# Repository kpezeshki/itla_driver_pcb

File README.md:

Board is generally functional but improvements are possible:

1. The hole size for the meanwell power supply modules is too small, so the modules need to be hacked to fit.

2. The UART module is too far from the board edge. Need to check footprint and shift closer.

Use a 40 mm half-height fan to cool the ITLA.

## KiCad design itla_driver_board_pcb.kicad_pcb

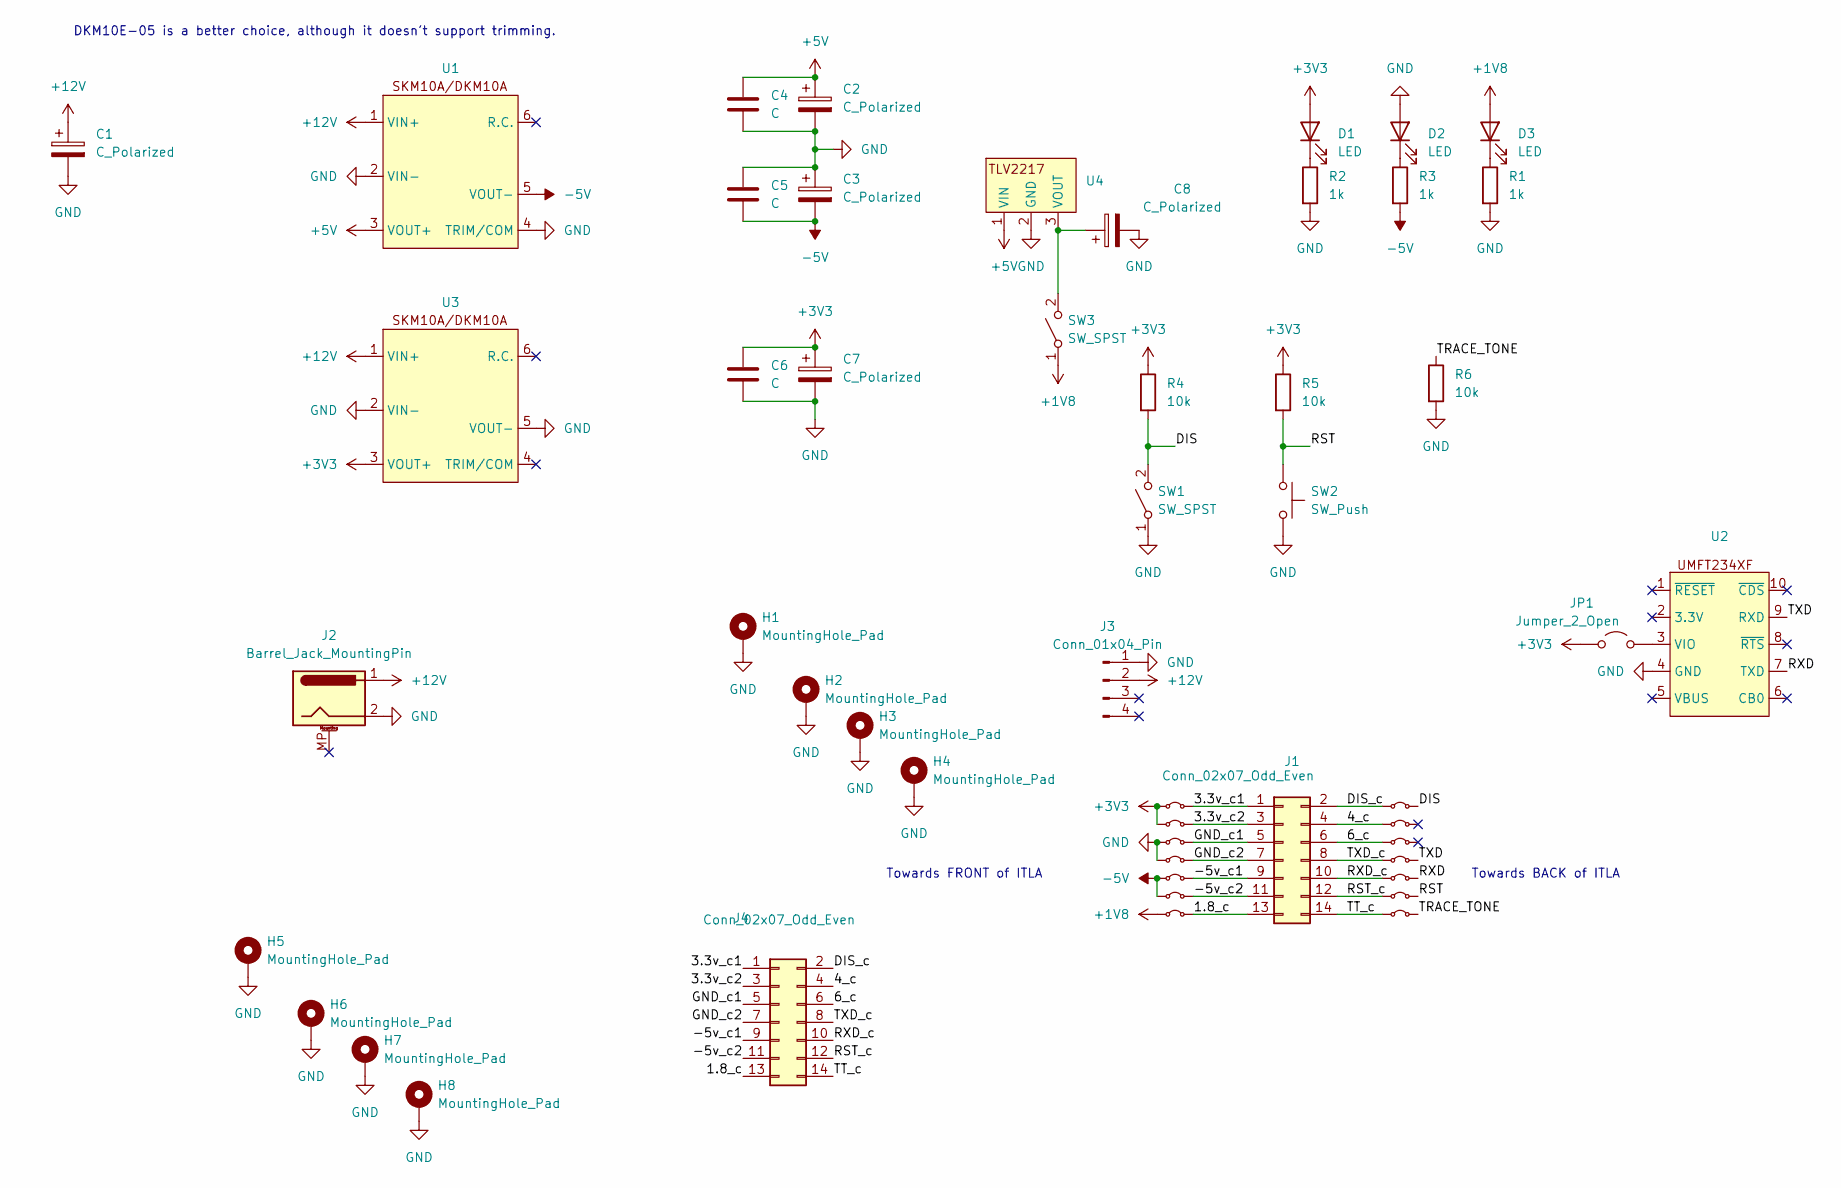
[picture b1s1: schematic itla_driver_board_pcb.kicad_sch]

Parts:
C1, C2, C3, C7, C8: C_Polarized; CP_Radial_D12.5mm_P5.00mm
C4, C5, C6: C; C_Disc_D10.0mm_W2.5mm_P5.00mm
D1, D2, D3: LED; LED_D5.0mm
H1, H2, H3, H4, H5, H6, H7, H8: MountingHole_Pad; MountingHole_3.2mm_M3_Pad
J1: Conn_02x07_Odd_Even; PinHeader_2x07_P1.00mm_Vertical_SMD
J2: Barrel_Jack_MountingPin; BarrelJack_CUI_PJ-063AH_Horizontal
J3: Conn_01x04_Pin; PinHeader_1x04_P2.54mm_Vertical
J4: Conn_02x07_Odd_Even; ITLA
JP1: Jumper_2_Open; SolderJumper-2_P1.3mm_Open_Pad1.0x1.5mm
JP2, JP3, JP4, JP5, JP6, JP7, JP8, JP9, JP10, JP11, JP12, JP13, JP14, JP15: Jumper_2_Small_Bridged; SolderJumper-2_P1.3mm_Bridged_Pad1.0x1.5mm
R1, R2, R3: 1k; R_Axial_DIN0207_L6.3mm_D2.5mm_P7.62mm_Horizontal
R4, R5, R6: 10k; R_Axial_DIN0207_L6.3mm_D2.5mm_P7.62mm_Horizontal
SW1, SW3: SW_SPST; SW_E-Switch_EG1271_SPDT
SW2: SW_Push; SW_SPST_Omron_B3F-40xx
U1, U3: SKM10
U2: UMFT234XF
U4: TO-220-3_Vertical

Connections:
+1V8: D3.2 (A), JP15.1 (A), SW3.1 (A)
+3V3: C6.1, C7.1, D1.2 (A), JP1.1 (A), JP9.1 (A), JP10.1 (A), R4.1, R5.1, U3.3 (VOUT+)
+5V: C2.1, C4.1, U1.3 (VOUT+), U4.1 (VIN)
+12V: C1.1, J2.1, J3.2, U1.1 (VIN+), U3.1 (VIN+)
-5V: C3.2, C5.2, JP13.1 (A), JP14.1 (A), R3.2, U1.5 (VOUT-)
/1.8_c: J1.13, J4.13, JP15.2 (B)
/3.3v_c1: J1.1, J4.1, JP9.2 (B)
/3.3v_c2: J1.3, J4.3, JP10.2 (B)
/4_c: J1.4, J4.4, JP7.1 (A)
/6_c: J1.6, J4.6, JP8.1 (A)
/-5v_c1: J1.9, J4.9, JP13.2 (B)
/-5v_c2: J1.11, J4.11, JP14.2 (B)
/DIS: JP2.2 (B), R4.2, SW1.2 (B)
/DIS_c: J1.2, J4.2, JP2.1 (A)
/GND_c1: J1.5, J4.5, JP11.2 (B)
/GND_c2: J1.7, J4.7, JP12.2 (B)
/RST: JP5.2 (B), R5.2, SW2.1
/RST_c: J1.12, J4.12, JP5.1 (A)
/RXD: JP4.2 (B), U2.7 (TXD)
/RXD_c: J1.10, J4.10, JP4.1 (A)
/TRACE_TONE: JP6.2 (B), R6.1
/TT_c: J1.14, J4.14, JP6.1 (A)
/TXD: JP3.2 (B), U2.9 (RXD)
/TXD_c: J1.8, J4.8, JP3.1 (A)
GND: C1.2, C2.2, C3.1, C4.2, C5.1, C6.2, C7.2, C8.2, D2.2 (A), H1.1, H2.1, H3.1, H4.1, H5.1, H6.1, H7.1, H8.1, J2.2, J3.1, JP11.1 (A), JP12.1 (A), R1.2, R2.2, R6.2, SW1.1 (A), SW2.2, U1.2 (VIN-), U1.4 (TRIM/COM), U2.4 (GND), U3.2 (VIN-), U3.5 (VOUT-), U4.2 (GND)
unnamed: D1.1 (K), R2.1
unnamed: D2.1 (K), R3.1
unnamed: D3.1 (K), R1.1
unnamed: JP1.2 (B), U2.3 (VIO)
unnamed: C8.1, SW3.2 (B), U4.3 (VOUT)

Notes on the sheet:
Towards FRONT of ITLA
DKM10E-05 is a better choice, although it doesn't support trimming.
Towards BACK of ITLA

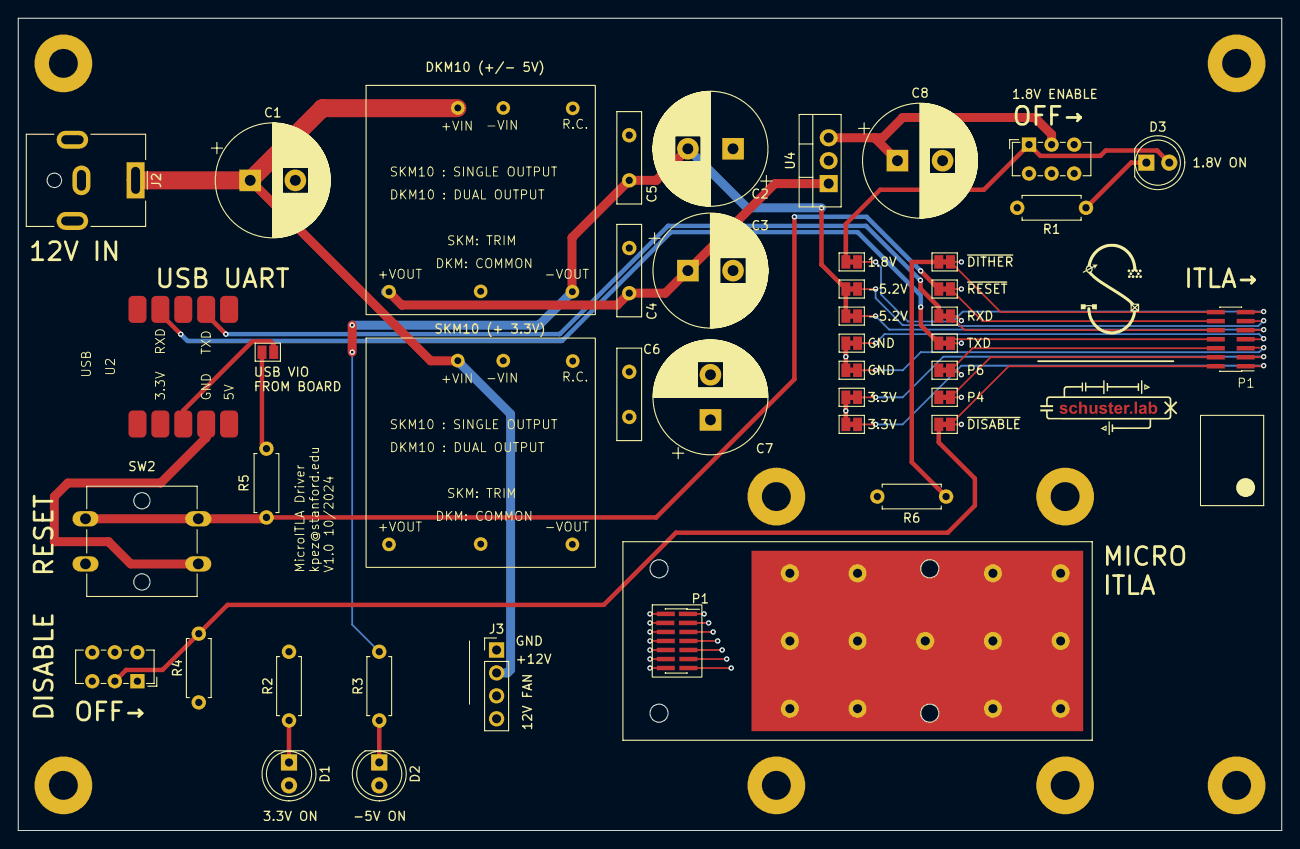
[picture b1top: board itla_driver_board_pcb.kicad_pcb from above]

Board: 4 copper layers, 140.0 x 90.0 mm, 51 parts (0 on the bottom side), 30 nets.

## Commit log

2024-10-25 added PCB design files
